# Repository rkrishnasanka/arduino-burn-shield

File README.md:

# Arduino Burn Shield

## Overview

This is the Arduino shield used for burning the Arduino boot-loader and program the Arduino programs onto the microcontroller

### PCB - Bottom

### PCB - Top

## Instructions to use the Shield

### Step 0 - Burn the bootloader

TBA

### Step 1 - Programming the Arduino as a Programmer

1. Select the `File->Examples->11. ArduioISP->ArdunioISP` sketch.
1. Verify
1. Upload

### Step 2 - Burning the program into ATTiny

1. Select `Tools->Board->ATtiny Microcontroller->ATtiny25/45/85` as the board. (**Note:** this option will only appear when we add the board using the board manager)
1. Select `Tools->Processor->ATtiny??` 
1. Select `Tools->Clock->??`
1. Select `Tools->Programmer->Arduino as ISP`

## References

1. AVR <-> Arduino Pin Map - [link](https://learn.sparkfun.com/tutorials/tiny-avr-programmer-hookup-guide/attiny85-use-hints)

2. ATTiny Arduino Tutorial (including the original schematics) - [link](https://makersportal.com/blog/2018/5/19/attiny85-arduino-board-how-to-flash-the-arduino-bootloader-and-run-a-simple-sketch)

## License

<br /><span xmlns:dct="http://purl.org/dc/terms/" property="dct:title">Arduino Burn Shield</span> by <a xmlns:cc="http://creativecommons.org/ns#" href="https://github.com/rkrishnasanka/arduino-burn-shield" property="cc:attributionName" rel="cc:attributionURL">Radhakrishna Sanka</a> is licensed under a <a rel="license" href="http://creativecommons.org/licenses/by/4.0/">Creative Commons Attribution 4.0 International License</a>.<br />Based on a work at <a xmlns:dct="http://purl.org/dc/terms/" href="https://makersportal.com/blog/2018/5/19/attiny85-arduino-board-how-to-flash-the-arduino-bootloader-and-run-a-simple-sketch" rel="dct:source">https://makersportal.com/blog/2018/5/19/attiny85-arduino-board-how-to-flash-the-arduino-bootloader-and-run-a-simple-sketch</a>.<br />Permissions beyond the scope of this license may be available at <a xmlns:cc="http://creativecommons.org/ns#" href="https://github.com/rkrishnasanka/arduino-burn-shield/LICENSE.md" rel="cc:morePermissions">https://github.com/rkrishnasanka/arduino-burn-shield/LICENSE.md</a>.

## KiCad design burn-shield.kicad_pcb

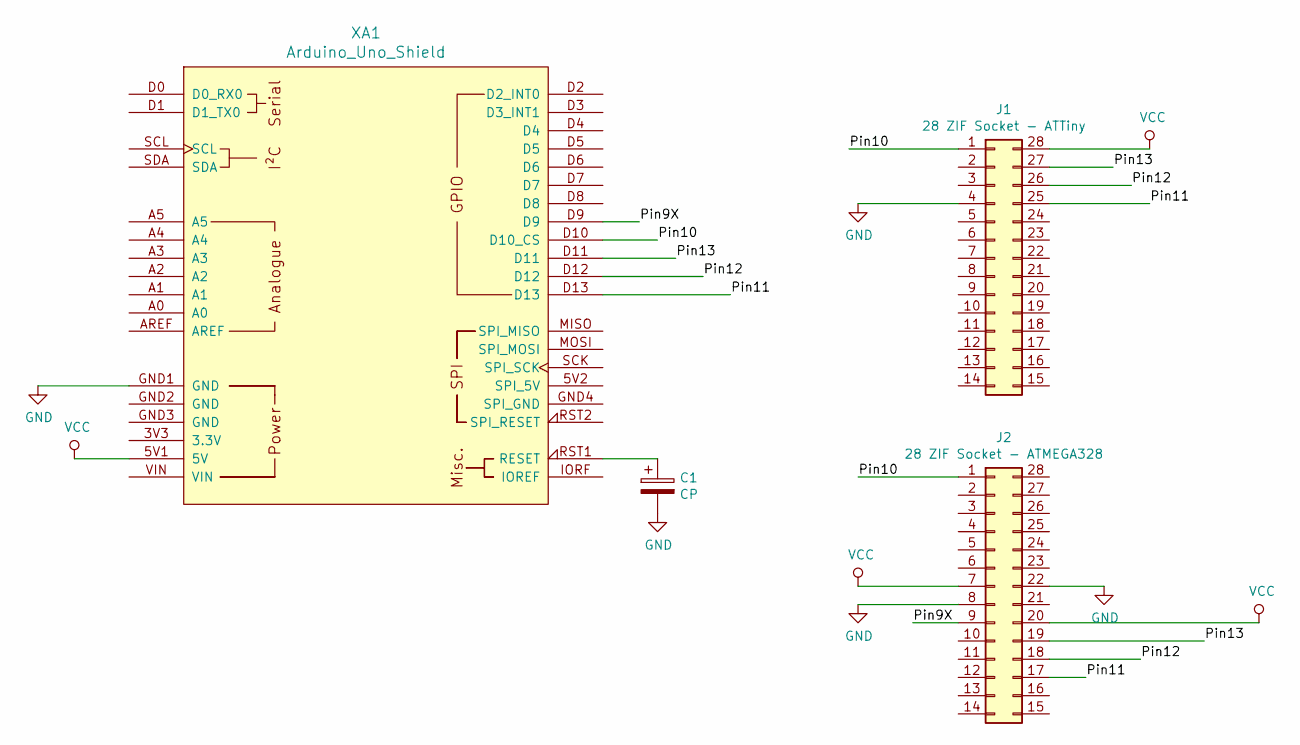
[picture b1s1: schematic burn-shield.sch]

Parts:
C1: CP; CP_Radial_D4.0mm_P2.00mm
J1: 28 ZIF Socket - ATTiny; DIP-28_296_ELL
J2: 28 ZIF Socket - ATMEGA328; DIP-28_296_ELL
XA1: Arduino_Uno_Shield

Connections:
/Pin9X: J2.9, XA1.D9
/Pin10: J1.1, J2.1, XA1.D10 (D10_CS)
/Pin11: J1.25, J2.17, XA1.D13
/Pin12: J1.26, J2.18, XA1.D12
/Pin13: J1.27, J2.19, XA1.D11
GND: C1.2, J1.4, J2.8, J2.22, XA1.GND1 (GND)
unnamed: C1.1, XA1.RST1 (RESET)
VCC: J1.28, J2.7, J2.20, XA1.5V1 (5V)

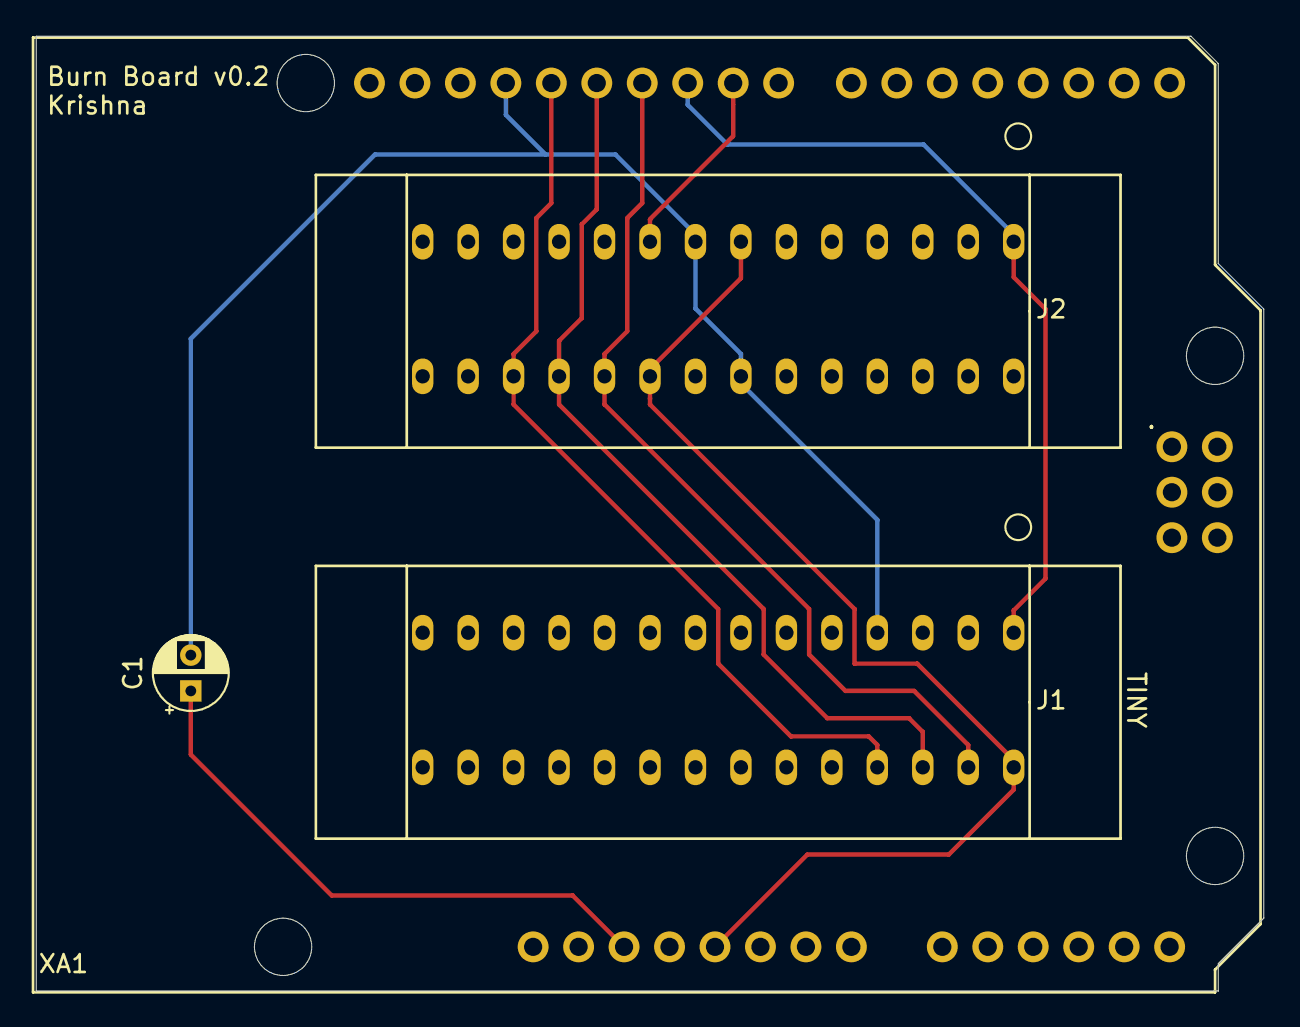
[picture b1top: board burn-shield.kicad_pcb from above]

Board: 2 copper layers, 68.6 x 53.3 mm, 4 parts (0 on the bottom side), 8 nets.

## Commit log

2020-12-30 Initial commit + ATTiny Version of the board
2020-12-30 Added the ATMEGA support too
2020-12-30 Updated the pcb
2020-12-30 Added the README for the data
